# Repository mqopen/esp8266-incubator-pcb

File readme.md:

# ESP8266 Incubator PCB
Design of ESP8266 incubator PCB.

## Features

  * Powered by mini DC-DC power supply module ([LM2596](http://www.ti.com/lit/ds/symlink/lm2596.pdf) chip).
  * 5.5 mm center positive jack.
  * On-board programming connector.
  * Programming push button.
  * Jumper for enabling power supply module.
  * RJ-11 connector for connecting various sensors.
  * Notification LED.
  * Intended to be manufactured by [dirtypcbs.com](http://dirtypcbs.com/).
  * AVR like ISP header for in circuit programming.
  * Two relays in series for driving heater circuit.
  * Two screw terminals for connecting heaters.
  * 12V screw terminal for controlling fan.
  * Piezo buzzer for alarm signaling.

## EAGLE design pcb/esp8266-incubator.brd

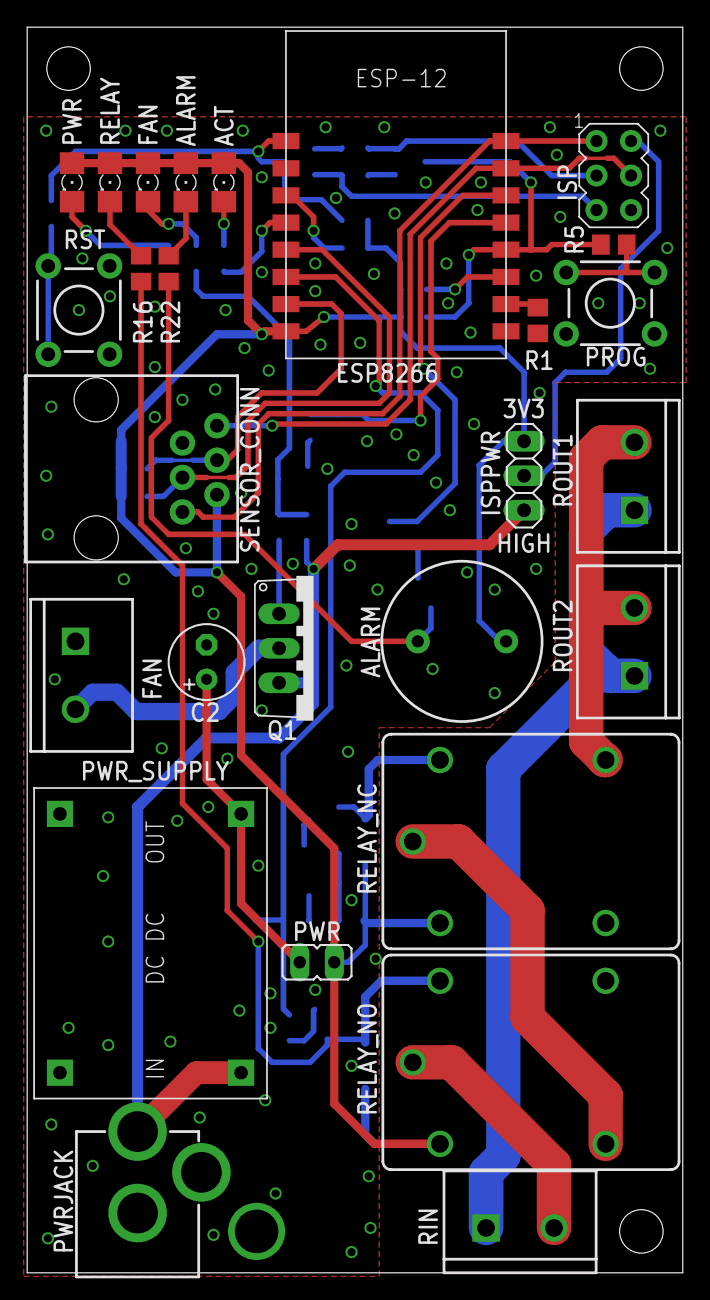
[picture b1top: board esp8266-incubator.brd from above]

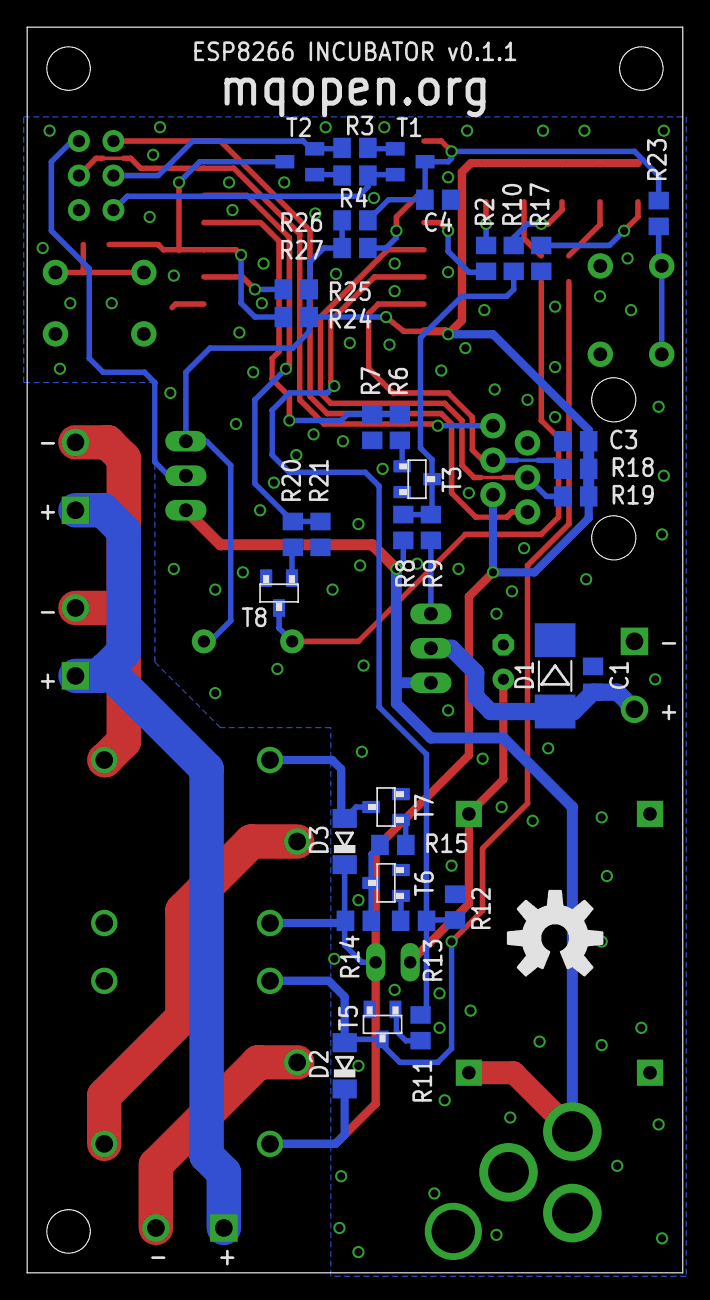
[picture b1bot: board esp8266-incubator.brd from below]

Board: 2 copper layers, 48.3 x 91.7 mm, 64 parts (37 on the bottom side), 45 nets.

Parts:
ACT_LED: RED; 1206
ALARM: BUZZERPTH; BUZZER-12MM
ALARM_LED: RED; 1206
C1: 1000nF; C0805
C2: 220uF; E2,5-6
C3, C4: 100nF; C0805
D1: 1N4007; MELF-MLL41
D2, D3: LL4148; SOD80C
ESP8266: ESP8266_ESP-12; ESP8266-ESP12
FAN: SCREWTERMINAL-5MM-2
FAN_LED: RED; 1206
ISP: AVRISP-6; AVRISP
ISPPWR: 1X03
PROG: TACTILE-PTH
PWR: JP1
PWRJACK: POWER_JACKPTH; POWER_JACK_PTH
PWR_LED: RED; 1206
PWR_SUPPLY: DC-DC-SMALL; DC-DC
Q1: IRF9540N; TO220V
R1, R3, R4, R7, R8, R12, R14, R18, R19, R21, R24, R25, R26, R27: 10K; R0805
R2, R17: 82R; R0805
R5, R23: 470R; R0805
R6, R9, R11, R13, R15, R20: 100R; R0805
R10, R16, R22: 1K; R0805
RELAY_LED: RED; 1206
RELAY_NC: JS-M1-12V-5; JS-M
RELAY_NO: JS-M1-12V-5; JS-M
RIN: SCREWTERMINAL-5MM-2
ROUT1, ROUT2: SCREWTERMINAL-5MM-2
RST: TACTILE-PTH
SENSOR_CONN: RJ11; RJ11-6
T1, T2: S8050; SOT23-BEC
T3, T5, T6, T7, T8: BSS138L; SOT23
U$1000: OSHW-LOGOL; OSHW-LOGO-L

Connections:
+3V3: ACT_LED.A, ALARM.+, ALARM_LED.A, C3.2, D2.C, D3.C, ESP8266.16, FAN_LED.A, ISPPWR.1, PWR.2, PWR_LED.A, R14.1, R18.2, R19.2, R24.2, R25.2, R26.2, R27.2, RELAY_LED.A, RELAY_NC.1, RELAY_NO.1, SENSOR_CONN.5
+12V: ISPPWR.3, PWRJACK.PWR, PWR_SUPPLY.P$1, Q1.3, R8.1
BUZZER: ESP8266.6, R20.2, R21.1
C230: RIN.1, ROUT1.1, ROUT2.1
DTR: ISP.3, R3.2, T2.E
EN: ESP8266.11, R27.1
FAN: ESP8266.5, R6.2, R7.1
GND: C1.1, C2.-, C3.1, C4.1, D1.C, ESP8266.1, FAN.1, ISP.6, PROG.3, PROG.4, PWRJACK.GND, PWRJACK.GNDBREAK, PWR_SUPPLY.P$3, PWR_SUPPLY.P$4, R1.2, R7.2, R12.2, R17.2, R21.2, RST.3, RST.4, SENSOR_CONN.2, T3.2, T5.2, T6.2, T7.2, T8.2
GPIO0: ESP8266.4, R5.1, R24.1, T2.C
GPIO2: ESP8266.3, R25.1
GPIO13: ESP8266.15, R18.1, SENSOR_CONN.3
GPIO14: ESP8266.13, R19.1, SENSOR_CONN.4
GPIO16: ESP8266.12, R2.2
unnamed: ACT_LED.C, R2.1
unnamed: C2.+, PWR.1, PWR_SUPPLY.P$2
unnamed: R3.1, T1.B
unnamed: PROG.1, PROG.2, R5.2
unnamed: ESP8266.2, R1.1
unnamed: ISP.2, ISPPWR.2
unnamed: R4.1, T2.B
unnamed: R20.1, T8.1
unnamed: D2.A, R16.2, RELAY_NO.2, T5.3
unnamed: R11.1, T5.1
unnamed: R13.1, T6.1
unnamed: R14.2, R15.2, T6.3
unnamed: R15.1, T7.1
unnamed: R16.1, RELAY_LED.C
unnamed: D3.A, RELAY_NC.2, T7.3
unnamed: RELAY_NC.C, RELAY_NO.NO
unnamed: Q1.1, R9.1
unnamed: ALARM_LED.C, R22.1
unnamed: ALARM.-, R22.2, T8.3
unnamed: PWR_LED.C, R17.1
unnamed: FAN_LED.C, R10.1
unnamed: R6.1, T3.1
unnamed: R8.2, R9.2, R10.2, T3.3
unnamed: C1.2, D1.A, FAN.2, Q1.2
unnamed: R23.2, RST.1, RST.2
NRST: C4.2, ESP8266.9, R23.1, R26.1, T1.C
P230: RELAY_NO.C, RIN.2
R230: RELAY_NC.NC, ROUT1.2, ROUT2.2
RELAY: ESP8266.14, R11.2, R12.1, R13.2
RST: ISP.5, R4.2, T1.E
RXD: ESP8266.7, ISP.4, SENSOR_CONN.1
TXD: ESP8266.8, ISP.1, SENSOR_CONN.6

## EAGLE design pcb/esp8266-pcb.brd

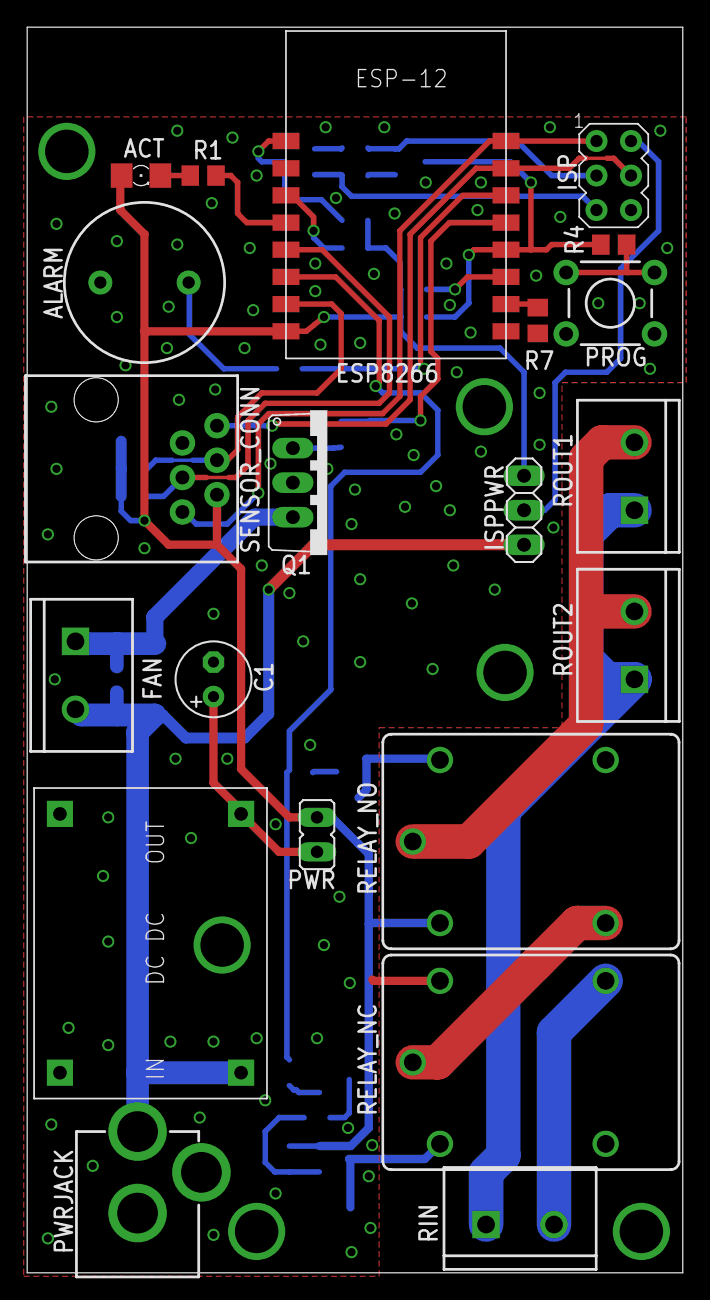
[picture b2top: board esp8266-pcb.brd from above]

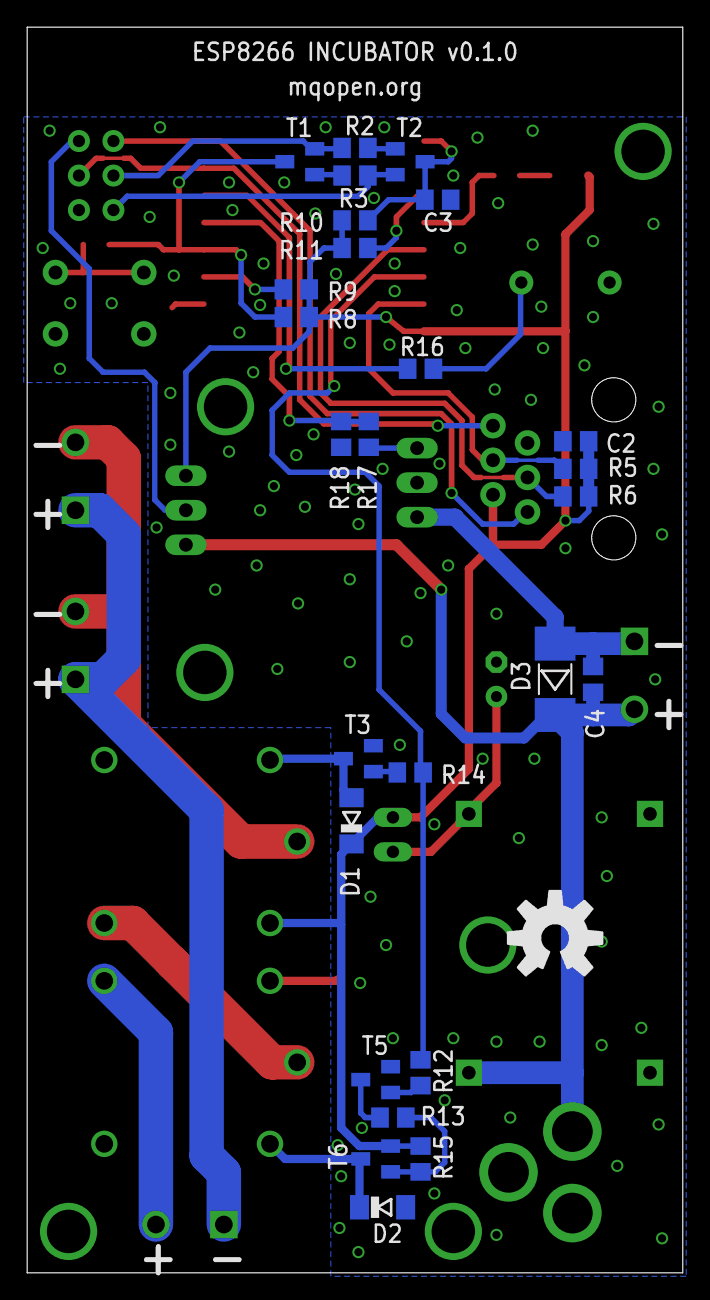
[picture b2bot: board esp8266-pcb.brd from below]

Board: 2 copper layers, 48.3 x 91.7 mm, 48 parts (27 on the bottom side), 37 nets.

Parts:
ACT: RED; 1206
ALARM: BUZZERPTH; BUZZER-12MM
C1: 220uF; E2,5-6
C2, C3, C4: 100nF; C0805
D1, D2: PMLL4150; SOD80C
D3: MELF-MLL41
ESP8266: ESP8266_ESP-12; ESP8266-ESP12
FAN: SCREWTERMINAL-5MM-2
ISP: AVRISP-6; AVRISP
ISPPWR: 1X03
PROG: TACTILE-PTH
PWR: JP1
PWRJACK: POWER_JACKPTH; POWER_JACK_PTH
Q1: MOSFET-PGDS_TO220V; TO220V
R1: 82R; R0805
R2, R3, R7, R8, R9, R10, R11, R12, R13, R14, R15, R17, R18: 12K; R0805
R4: 470R; R0805
R5, R6: 10K; R0805
R16: 100; R0805
RELAY_NC: JS-M1-12V-5; JS-M
RELAY_NO: JS-M1-12V-5; JS-M
RIN: SCREWTERMINAL-5MM-2
ROUT1, ROUT2: SCREWTERMINAL-5MM-2
SENSOR_CONN: RJ11; RJ11-6
T1, T2, T3, T5, T6: SOT23-BEC
U$1: OSHW-LOGOL; OSHW-LOGO-L
U$2: DC-DC-SMALL; DC-DC

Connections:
+3V3: ACT.A, C2.2, D1.C, ESP8266.16, ISPPWR.1, PWR.2, R5.2, R6.2, R8.2, R9.2, R10.2, R11.2, R15.1, RELAY_NO.1, SENSOR_CONN.5, T6.E
+12V: C4.2, D3.C, FAN.2, ISPPWR.3, PWRJACK.PWR, U$2.P$1
BUZZER: ESP8266.6, R16.2
C230: RIN.1, ROUT1.1, ROUT2.1
DTR: ISP.3, R2.2, T1.E
EN: ESP8266.11, R11.1
FAN: ESP8266.5, R17.2, R18.2
FANOUT: C4.1, D3.A, FAN.1, Q1.3
GND: ALARM.-, C1.-, C2.1, C3.1, D2.A, ESP8266.1, ISP.6, PROG.3, PROG.4, PWRJACK.GND, PWRJACK.GNDBREAK, Q1.2, R7.2, R18.1, RELAY_NC.2, SENSOR_CONN.2, T3.E, T5.E, U$2.P$3, U$2.P$4
GPIO0: ESP8266.4, R4.1, R8.1, T1.C
GPIO2: ESP8266.3, R9.1
GPIO13: ESP8266.15, R5.1, SENSOR_CONN.3
GPIO14: ESP8266.13, R6.1, SENSOR_CONN.4
GPIO16: ESP8266.12, R1.2
unnamed: ACT.C, R1.1
unnamed: C1.+, PWR.1, U$2.P$2
unnamed: R2.1, T2.B
unnamed: PROG.1, PROG.2, R4.2
unnamed: ESP8266.2, R7.1
unnamed: ISP.2, ISPPWR.2
unnamed: R3.1, T1.B
unnamed: ALARM.+, R16.1
unnamed: D1.A, RELAY_NO.2, T3.C
unnamed: R14.1, T3.B
unnamed: R12.1, T5.B
unnamed: R13.2, T5.C
unnamed: R13.1, R15.2, T6.B
unnamed: D2.C, RELAY_NC.1, T6.C
unnamed: RELAY_NC.C, RELAY_NO.NO
unnamed: Q1.1, R17.1
NRST: C3.2, ESP8266.9, R10.1, T2.C
P230: RELAY_NC.NC, RIN.2
R230: RELAY_NO.C, ROUT1.2, ROUT2.2
RELAY: ESP8266.14, R12.2, R14.2
RST: ISP.5, R3.2, T2.E
RXD: ESP8266.7, ISP.4, SENSOR_CONN.1
TXD: ESP8266.8, ISP.1, SENSOR_CONN.6

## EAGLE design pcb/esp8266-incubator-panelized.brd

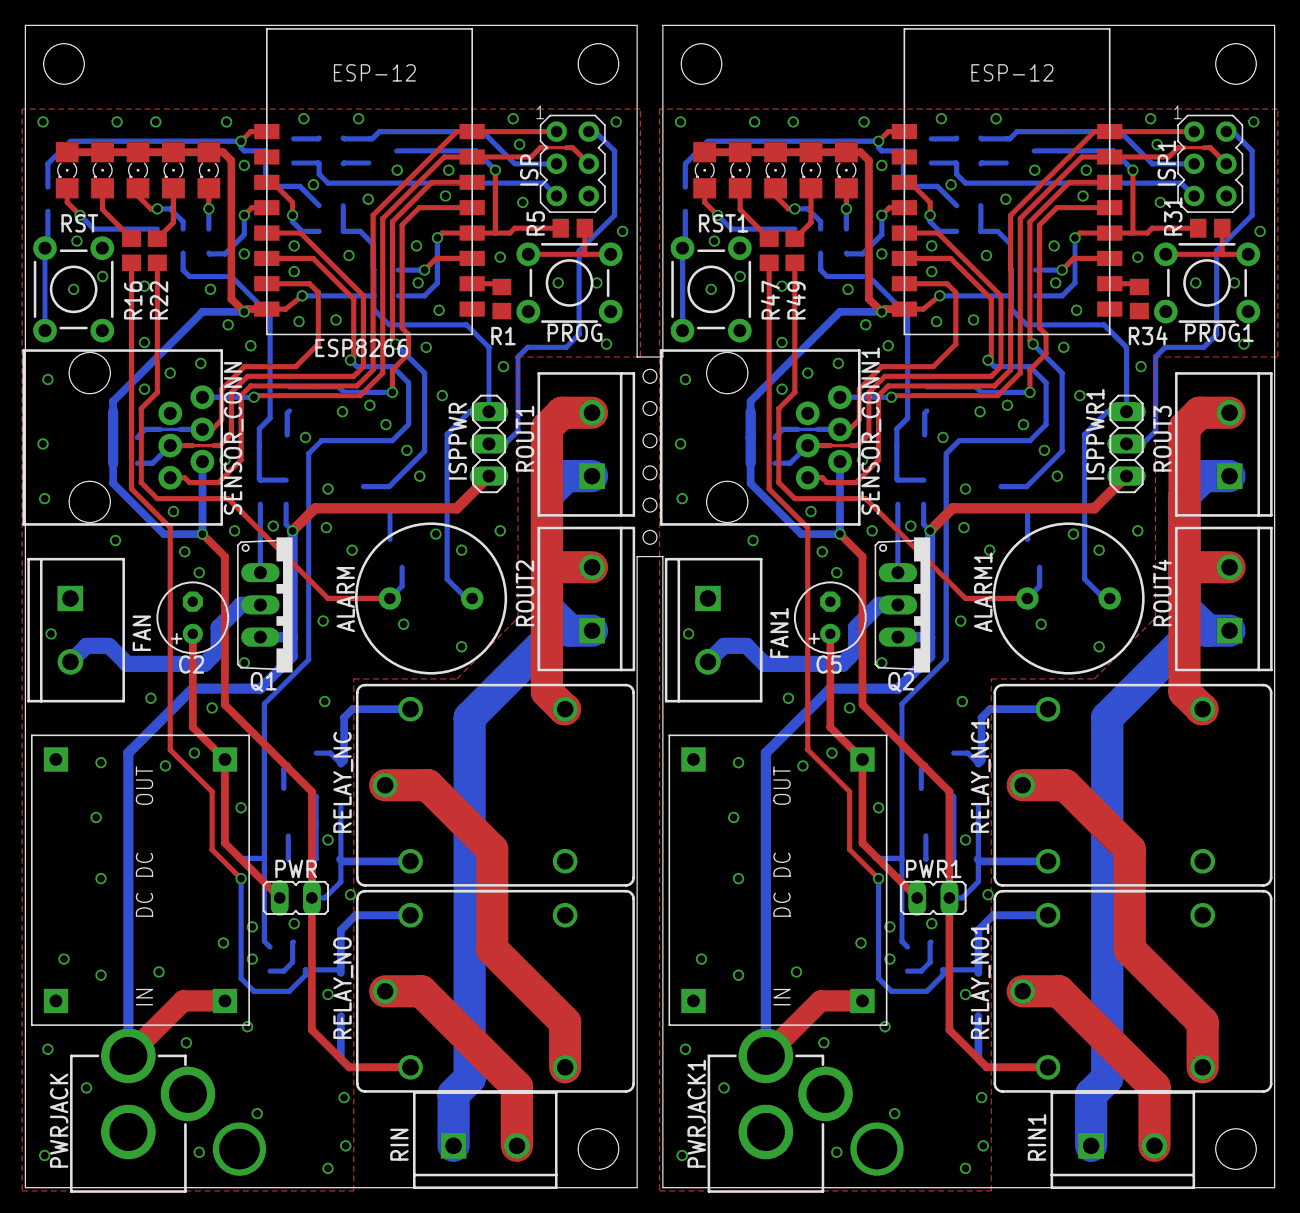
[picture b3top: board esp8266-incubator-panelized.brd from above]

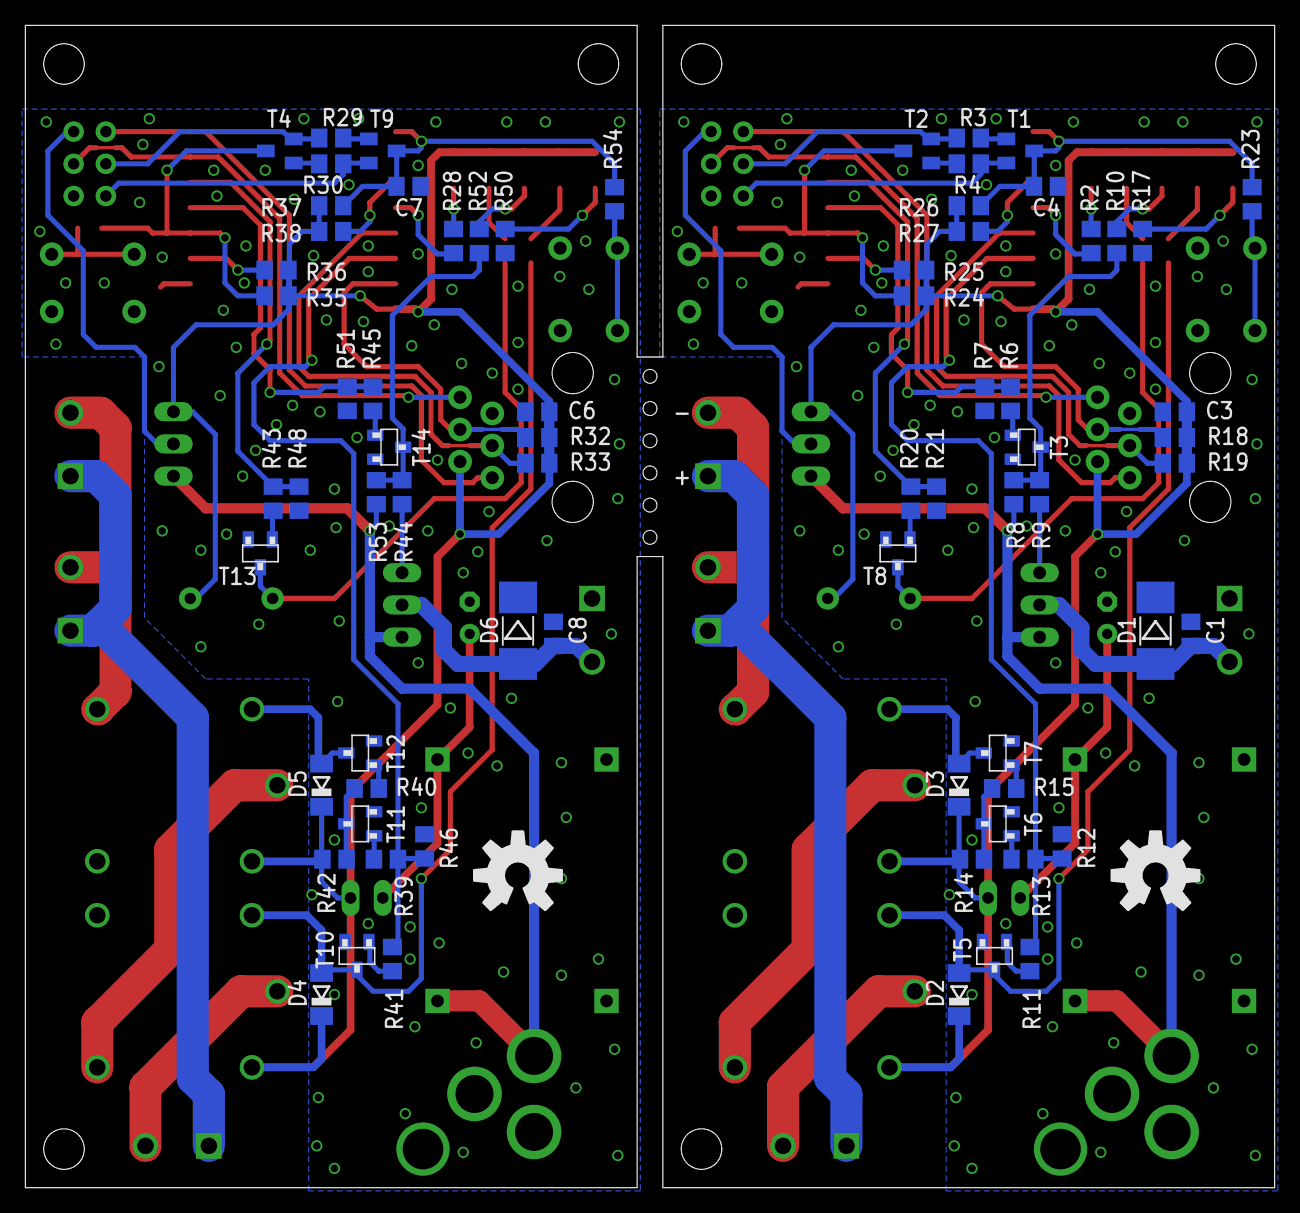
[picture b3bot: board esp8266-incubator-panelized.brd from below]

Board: 2 copper layers, 98.6 x 91.7 mm, 128 parts (74 on the bottom side), 90 nets.

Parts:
ACT_LED, ACT_LED1: RED; 1206
ALARM, ALARM1: BUZZERPTH; BUZZER-12MM
ALARM_LED, ALARM_LED1: RED; 1206
C1, C8: 1000nF; C0805
C2, C5: 220uF; E2,5-6
C3, C4, C6, C7: 100nF; C0805
D1, D6: 1N4007; MELF-MLL41
D2, D3, D4, D5: LL4148; SOD80C
ESP1, ESP8266: ESP8266_ESP-12; ESP8266-ESP12
FAN, FAN1: SCREWTERMINAL-5MM-2
FAN_LED, FAN_LED1: RED; 1206
ISP, ISP1: AVRISP-6; AVRISP
ISPPWR, ISPPWR1: 1X03
PROG, PROG1: TACTILE-PTH
PWR, PWR1: JP1
PWRJACK, PWRJACK1: POWER_JACKPTH; POWER_JACK_PTH
PWR_LED, PWR_LED1: RED; 1206
PWR_SUPPLY, PWR_SUPPLY1: DC-DC-SMALL; DC-DC
Q1, Q2: IRF9540N; TO220V
R1, R3, R4, R24, R25, R26, R27, R29, R30, R34, R35, R36, R37, R38: 12K; R0805
R2, R17, R28, R50: 82R; R0805
R5, R23, R31, R54: 470R; R0805
R6, R9, R11, R13, R15, R20, R39, R40, R41, R43, R44, R45: 100R; R0805
R7, R8, R12, R14, R18, R19, R21, R32, R33, R42, R46, R48, R51, R53: 10K; R0805
R10, R16, R22, R47, R49, R52: 1K; R0805
RELAY_LED, RELAY_LED1: RED; 1206
RELAY_NC, RELAY_NC1: JS-M1-12V-5; JS-M
RELAY_NO, RELAY_NO1: JS-M1-12V-5; JS-M
RIN, RIN1: SCREWTERMINAL-5MM-2
ROUT1, ROUT2, ROUT3, ROUT4: SCREWTERMINAL-5MM-2
RST, RST1: TACTILE-PTH
SENSOR_CONN, SENSOR_CONN1: RJ11; RJ11-6
T1, T2, T4, T9: S8050; SOT23-BEC
T3, T5, T6, T7, T8, T10, T11, T12, T13, T14: BSS138L; SOT23
U$1, U$1000: OSHW-LOGOL; OSHW-LOGO-L

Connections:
+3V1: ACT_LED1.A, ALARM1.+, ALARM_LED1.A, C6.2, D4.C, D5.C, ESP1.16, FAN_LED1.A, ISPPWR1.1, PWR1.2, PWR_LED1.A, R32.2, R33.2, R35.2, R36.2, R37.2, R38.2, R42.1, RELAY_LED1.A, RELAY_NC1.1, RELAY_NO1.1, SENSOR_CONN1.5
+3V3: ACT_LED.A, ALARM.+, ALARM_LED.A, C3.2, D2.C, D3.C, ESP8266.16, FAN_LED.A, ISPPWR.1, PWR.2, PWR_LED.A, R14.1, R18.2, R19.2, R24.2, R25.2, R26.2, R27.2, RELAY_LED.A, RELAY_NC.1, RELAY_NO.1, SENSOR_CONN.5
+12V: ISPPWR.3, PWRJACK.PWR, PWR_SUPPLY.P$1, Q1.3, R8.1
+12V1: ISPPWR1.3, PWRJACK1.PWR, PWR_SUPPLY1.P$1, Q2.3, R53.1
BUZZER: ESP8266.6, R20.2, R21.1
BUZZER1: ESP1.6, R43.2, R48.1
C1: RIN1.1, ROUT3.1, ROUT4.1
C230: RIN.1, ROUT1.1, ROUT2.1
DTR: ISP.3, R3.2, T2.E
DTR1: ISP1.3, R29.2, T4.E
EN: ESP8266.11, R27.1
EN1: ESP1.11, R38.1
FAN: ESP8266.5, R6.2, R7.1
FAN1: ESP1.5, R45.2, R51.1
GND: C1.1, C2.-, C3.1, C4.1, D1.C, ESP8266.1, FAN.1, ISP.6, PROG.3, PROG.4, PWRJACK.GND, PWRJACK.GNDBREAK, PWR_SUPPLY.P$3, PWR_SUPPLY.P$4, R1.2, R7.2, R12.2, R17.2, R21.2, RST.3, RST.4, SENSOR_CONN.2, T3.2, T5.2, T6.2, T7.2, T8.2
GND1: C5.-, C6.1, C7.1, C8.1, D6.C, ESP1.1, FAN1.1, ISP1.6, PROG1.3, PROG1.4, PWRJACK1.GND, PWRJACK1.GNDBREAK, PWR_SUPPLY1.P$3, PWR_SUPPLY1.P$4, R34.2, R46.2, R48.2, R50.2, R51.2, RST1.3, RST1.4, SENSOR_CONN1.2, T10.2, T11.2, T12.2, T13.2, T14.2
GPIO0: ESP8266.4, R5.1, R24.1, T2.C
GPIO1: ESP1.4, R31.1, R35.1, T4.C
GPIO2: ESP8266.3, R25.1
GPIO3: ESP1.12, R28.2
GPIO4: ESP1.13, R33.1, SENSOR_CONN1.4
GPIO5: ESP1.15, R32.1, SENSOR_CONN1.3
GPIO6: ESP1.3, R36.1
GPIO13: ESP8266.15, R18.1, SENSOR_CONN.3
GPIO14: ESP8266.13, R19.1, SENSOR_CONN.4
GPIO16: ESP8266.12, R2.2
unnamed: ACT_LED.C, R2.1
unnamed: C2.+, PWR.1, PWR_SUPPLY.P$2
unnamed: R3.1, T1.B
unnamed: PROG.1, PROG.2, R5.2
unnamed: ESP8266.2, R1.1
unnamed: ISP.2, ISPPWR.2
unnamed: R4.1, T2.B
unnamed: R20.1, T8.1
unnamed: D2.A, R16.2, RELAY_NO.2, T5.3
unnamed: ACT_LED1.C, R28.1
unnamed: R11.1, T5.1
unnamed: R13.1, T6.1
unnamed: R14.2, R15.2, T6.3
unnamed: R15.1, T7.1
unnamed: R16.1, RELAY_LED.C
unnamed: D3.A, RELAY_NC.2, T7.3
unnamed: RELAY_NC.C, RELAY_NO.NO
unnamed: Q1.1, R9.1
unnamed: ALARM_LED.C, R22.1
unnamed: ALARM.-, R22.2, T8.3
unnamed: PWR_LED.C, R17.1
unnamed: FAN_LED.C, R10.1
unnamed: R6.1, T3.1
unnamed: R8.2, R9.2, R10.2, T3.3
unnamed: C1.2, D1.A, FAN.2, Q1.2
unnamed: R23.2, RST.1, RST.2
unnamed: R29.1, T9.B
unnamed: R30.1, T4.B
unnamed: PROG1.1, PROG1.2, R31.2
unnamed: C5.+, PWR1.1, PWR_SUPPLY1.P$2
unnamed: ESP1.2, R34.1
unnamed: ISP1.2, ISPPWR1.2
unnamed: R41.1, T10.1
unnamed: D4.A, R47.2, RELAY_NO1.2, T10.3
unnamed: R39.1, T11.1
unnamed: R40.2, R42.2, T11.3
unnamed: R40.1, T12.1
unnamed: RELAY_NC1.C, RELAY_NO1.NO
unnamed: Q2.1, R44.1
unnamed: D5.A, RELAY_NC1.2, T12.3
unnamed: R47.1, RELAY_LED1.C
unnamed: R43.1, T13.1
unnamed: ALARM_LED1.C, R49.1
unnamed: ALARM1.-, R49.2, T13.3
unnamed: PWR_LED1.C, R50.1
unnamed: R45.1, T14.1
unnamed: FAN_LED1.C, R52.1
unnamed: R44.2, R52.2, R53.2, T14.3
unnamed: C8.2, D6.A, FAN1.2, Q2.2
unnamed: R54.2, RST1.1, RST1.2
NRST: C4.2, ESP8266.9, R23.1, R26.1, T1.C
NRST1: C7.2, ESP1.9, R37.1, R54.1, T9.C
P1: RELAY_NO1.C, RIN1.2
P230: RELAY_NO.C, RIN.2
R1: RELAY_NC1.NC, ROUT3.2, ROUT4.2
R230: RELAY_NC.NC, ROUT1.2, ROUT2.2
RELAY: ESP8266.14, R11.2, R12.1, R13.2
RELAY1: ESP1.14, R39.2, R41.2, R46.1
RST: ISP.5, R4.2, T1.E
RST1: ISP1.5, R30.2, T9.E
RXD: ESP8266.7, ISP.4, SENSOR_CONN.1
RXD1: ESP1.7, ISP1.4, SENSOR_CONN1.1
TXD: ESP8266.8, ISP.1, SENSOR_CONN.6
TXD1: ESP1.8, ISP1.1, SENSOR_CONN1.6

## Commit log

2016-08-10 Initial commit.
2016-11-28 Renamed source files.
2016-11-28 Added schematics PDF file.
2016-11-28 Added changelog.
2016-11-28 Added readme file and assembled board image.
2016-11-28 Updated readme.
2016-11-29 Designed new version schematics and board design.
2016-11-29 Added version number to all schematics sheets.
2016-11-29 Updated schematics PDF file.
2016-11-29 Fixed schematics PDF file.
2016-11-30 Updated LED labels.
2016-11-30 Added board image.
2016-11-30 Updated relay trace.
2016-11-30 Updated mounting holes.
2016-11-30 Design update.
2016-12-05 Added panelized board design.
2016-12-05 Updated .gitignore file. Removed ignore of gerber files.
2016-12-05 Added GERBER files.
2016-12-05 Added panelized board image.
2016-12-05 Hiden names layers.
2016-12-11 Updated some resistor values.

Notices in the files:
parts and their libraries:
SparkFun-Connectors: Licensing: Creative Commons ShareAlike 4.0 International - https://creativecommons.org/licenses/by-sa/4.0
SparkFun: Licensing: CC v3.0 Share-Alike You are welcome to use this library for commercial purposes.
